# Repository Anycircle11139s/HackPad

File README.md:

# HackPad
Thsi is my personal hackpad. It's my first time creating a hackpad and my first time creating a schematic, wiring a pcb and coding a keyboard.

I CAD-ed the case, I have a background in CADing so it wasn't too difficult, I spent a lot of time creating the intricate patterns on the case for the hackpad. I spent about 4 and a half hours on the CAD, simpliy because I spent a lot of time adding detail and making the case look better.

This is another image of the CAD, this time without the PCB, so you can see the back as well

This is a picture of my PCB, I spent a lot of time on this, I originally made it really small because I thought the limit was 60 by 80, that's why everything is squished together, after realising that the limit was 100 by 100, I decided to make it bigger bby including images and customizing it. I spent about 10 hours on the PCB because it was my first time making a PCB and I had to learn everything from scratch.

This is my schematic, this was the first thing I did and originally found it confusing, but after researching a lot and looking around in reddit, I found some reference images to help make the matrix and I also asked chatgpt a bit on how to route it. I spent about 5 hours on this mainly because of the research.

BOM:
8x Cherry MX Switches
1x XIAO RP2040
8x Blank DSA Keycaps
4x M3x16 Bolt
4x M3 Heatset
1x EC11 Rotary encoder with switch
1x 0.91 Oled display
8x SK6812 Mini RGB LEDs

Update:
I finished the build and due to blueprint closing, I'm prob gonna have to submit it to fallout. I think its really cool, I'm thinking that for the future, I can make the oled say inspirational quotes or smth but idk. This was my first hack club project and it was really fun, I had some trouble soldering the rgb leds, but thats fine. 

Here is a video of it working along with some images: asmr ahhh

https://github.com/user-attachments/assets/2c05eee1-dd40-4e33-92c0-3e3769b171cc

## BOM:
| Name                            | Purpose             | Quantity | Total (USD) | Link | Distributor |
|---------------------------------|---------------------|----------|-------------|------|-------------|
| Cherry MX switches              | Buttons for hackpad | 8        | 0           |      | Hackpad kit |
| Xiao rp2040                     | Microcontroller     | 1        | 0           |      | Hackpad kit |
| Blank DSA Keycaps               | Switch Covers       | 8        | 0           |      | Hackpad kit |
| M3x16 Bolt                      | Screws and bolts    | 4        | 0           |      | Hackpad kit |
| M3 Heatset                      | Heat inserts        | 4        | 0           |      | Hackpad kit |
| EC11 Rotary encoder with switch | Rotary encoder      | 1        | 0           |      | Hackpad kit |
| 0.91 Oled display               | Oled screen         | 1        | 0           |      | Hackpad kit |
| SK6812 Mini RGB LEDs            | Backlighting        | 8        | 0           |      | Hackpad kit |
|                                 |                     |          |             |      |             |

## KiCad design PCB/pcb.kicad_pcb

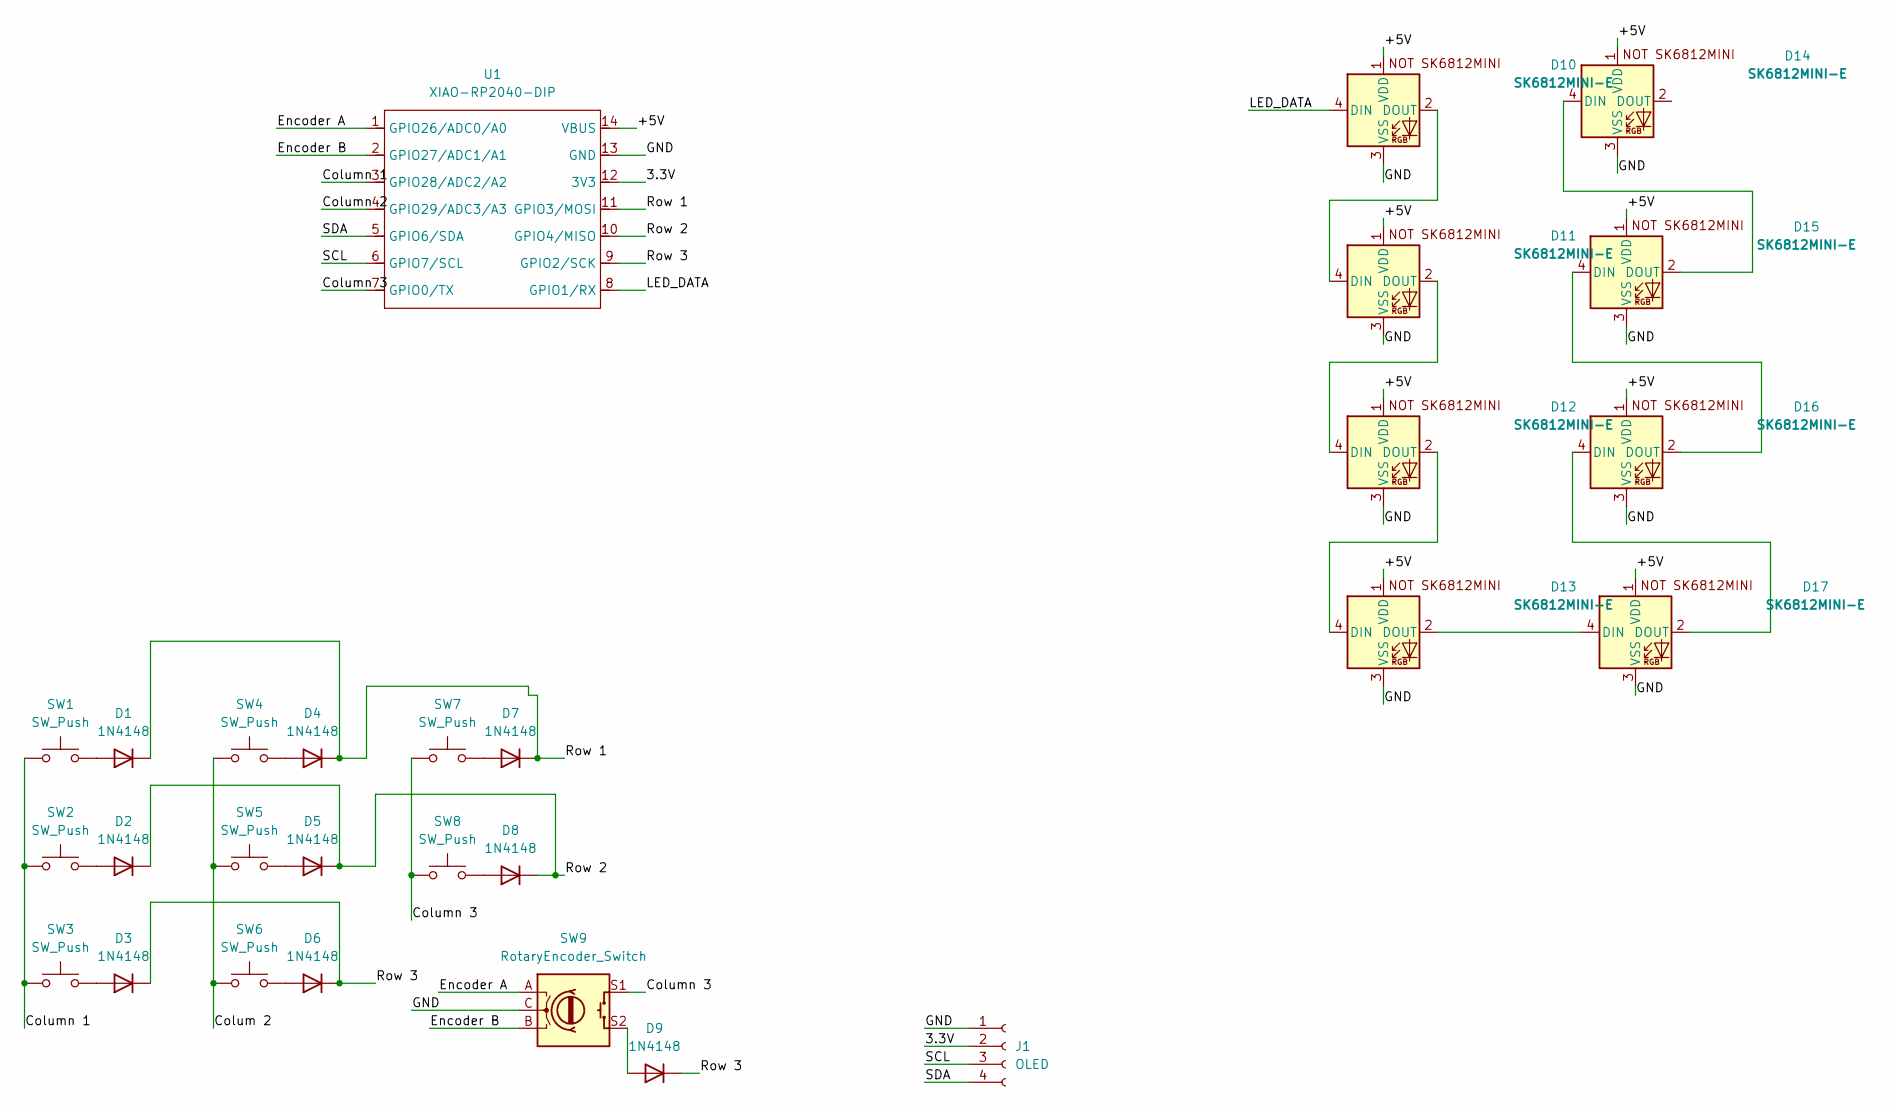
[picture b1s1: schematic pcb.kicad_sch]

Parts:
D1, D2, D3, D4, D5, D6, D7, D8, D9: 1N4148; D_DO-35_SOD27_P7.62mm_Horizontal
D10, D11, D12, D13, D14, D15, D16, D17: SK6812MINI-E; SK6812MINI-E Fixed
J1: OLED; SSD1306-0.91-OLED-4pin-128x32
SW1, SW2, SW3, SW4, SW5, SW6, SW7, SW8: SW_Push; SW_Cherry_MX_1.00u_PCB
SW9: RotaryEncoder_Switch; RotaryEncoder_Alps_EC11E-Switch_Vertical_H20mm
U1: XIAO-RP2040-DIP; XIAO-Generic-Hybrid-14P-2.54-21X17.8MM (1)

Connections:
/3.3V: J1.2, U1.12 (3V3)
/+5V: D10.1 (VDD), D11.1 (VDD), D12.1 (VDD), D13.1 (VDD), D14.1 (VDD), D15.1 (VDD), D16.1 (VDD), D17.1 (VDD), U1.14 (VBUS)
/Colum 2: SW4.1, SW5.1, SW6.1
/Column 1: SW1.1, SW2.1, SW3.1, U1.3 (GPIO28/ADC2/A2)
/Column 2: U1.4 (GPIO29/ADC3/A3)
/Column 3: SW7.1, SW8.1, SW9.S1, U1.7 (GPIO0/TX)
/Encoder A: SW9.A, U1.1 (GPIO26/ADC0/A0)
/Encoder B: SW9.B, U1.2 (GPIO27/ADC1/A1)
/GND: D10.3 (VSS), D11.3 (VSS), D12.3 (VSS), D13.3 (VSS), D14.3 (VSS), D15.3 (VSS), D16.3 (VSS), D17.3 (VSS), J1.1, SW9.C, U1.13 (GND)
/LED_DATA: D10.4 (DIN), U1.8 (GPIO1/RX)
/Row 1: D1.1 (K), D4.1 (K), D7.1 (K), U1.11 (GPIO3/MOSI)
/Row 2: D2.1 (K), D5.1 (K), D8.1 (K), U1.10 (GPIO4/MISO)
/Row 3: D3.1 (K), D6.1 (K), D9.1 (K), U1.9 (GPIO2/SCK)
/SCL: J1.3, U1.6 (GPIO7/SCL)
/SDA: J1.4, U1.5 (GPIO6/SDA)
unnamed: D1.2 (A), SW1.2
unnamed: D2.2 (A), SW2.2
unnamed: D3.2 (A), SW3.2
unnamed: D4.2 (A), SW4.2
unnamed: D5.2 (A), SW5.2
unnamed: D6.2 (A), SW6.2
unnamed: D7.2 (A), SW7.2
unnamed: D8.2 (A), SW8.2
unnamed: D9.2 (A), SW9.S2
unnamed: D10.2 (DOUT), D11.4 (DIN)
unnamed: D11.2 (DOUT), D12.4 (DIN)
unnamed: D12.2 (DOUT), D13.4 (DIN)
unnamed: D13.2 (DOUT), D17.4 (DIN)
unnamed: D14.4 (DIN), D15.2 (DOUT)
unnamed: D15.4 (DIN), D16.2 (DOUT)
unnamed: D16.4 (DIN), D17.2 (DOUT)

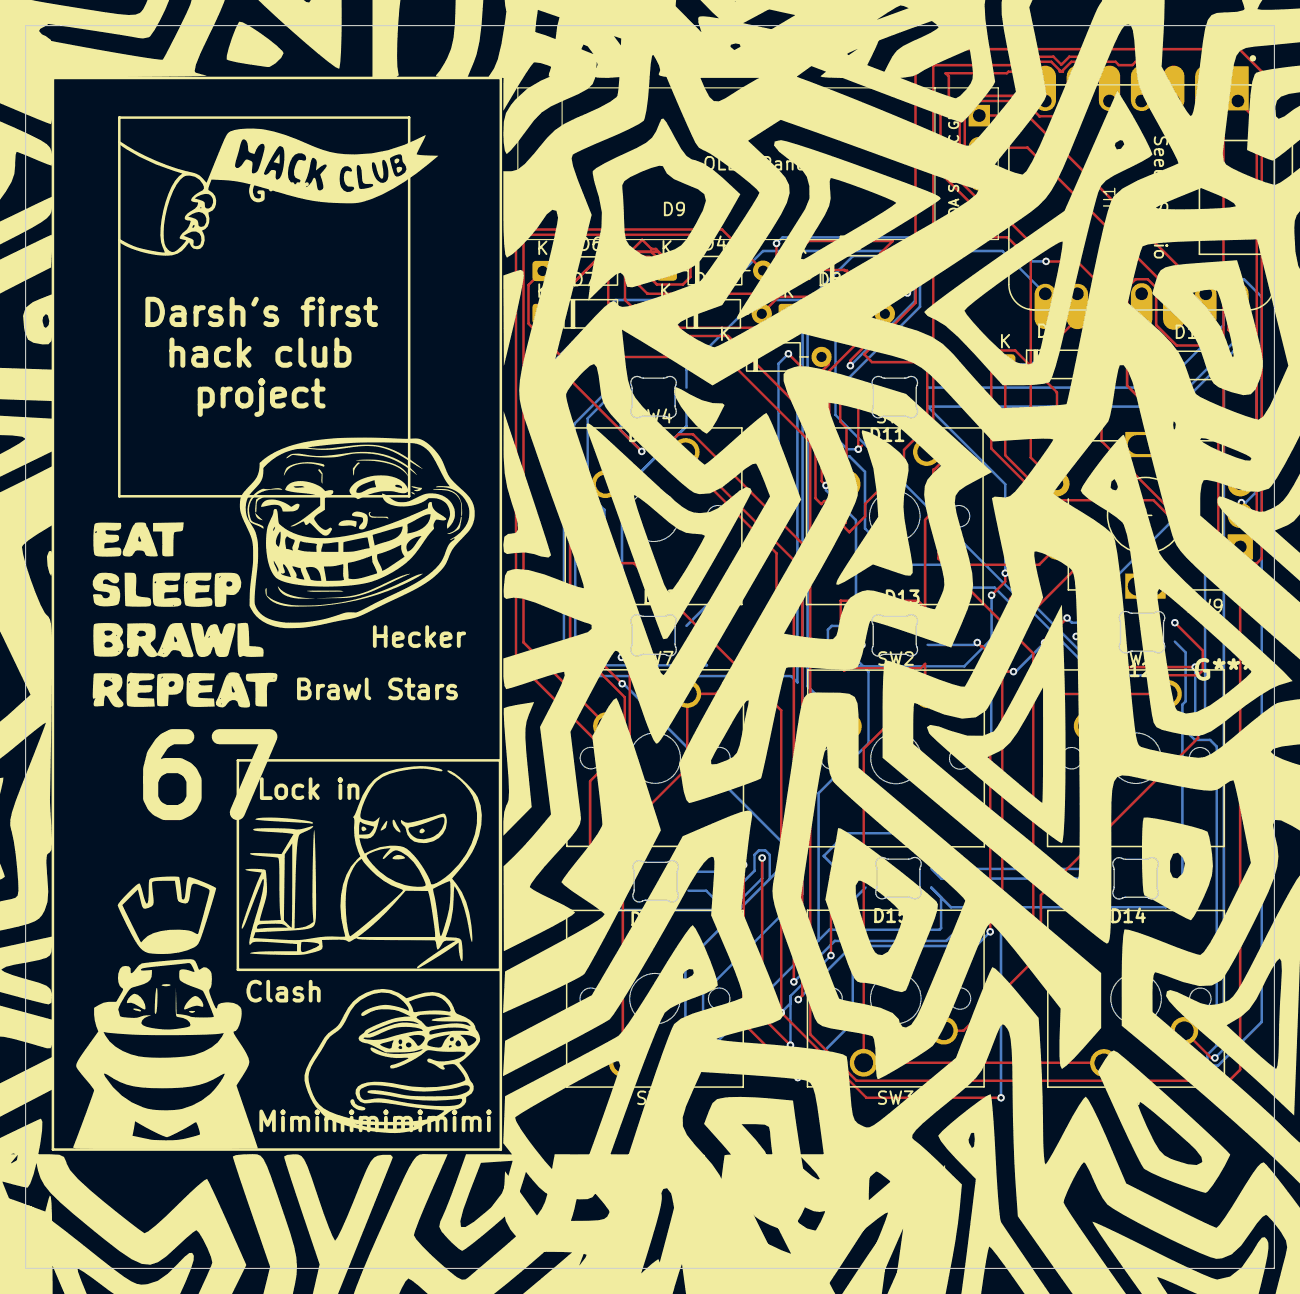
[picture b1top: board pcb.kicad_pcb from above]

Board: 2 copper layers, 98.7 x 98.3 mm, 33 parts (0 on the bottom side), 30 nets.

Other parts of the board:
Brawl Stars: LOGO
Clash: LOGO
Hecker: LOGO
Lock in: LOGO
Mimimimimimimi: LOGO

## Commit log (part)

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2026-02-17 Rename Final assembly.step to CAD/Final assembly.step
2026-02-17 Rename pcb.kicad_pro to PCB/pcb.kicad_pro
2026-03-09 Initialize keyboard with encoder and keymap
    Set up keyboard with encoder handling and media keys.
2026-03-09 Initialize keyboard with encoder and keymap
    Set up keyboard with encoder and media keys functionality.
2026-03-09 Rename pcb.kicad_pcb to PCB/pcb.kicad_pcb
2026-03-09 Rename pcb.kicad_sch to PCB/pcb.kicad_sch
2026-03-10 Refactor comments for clarity in main.py
